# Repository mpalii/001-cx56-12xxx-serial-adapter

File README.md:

# 001-cx56-12xxx-serial-adapter
SN64HC595 based serial adapter for Cx54-21xxx displays

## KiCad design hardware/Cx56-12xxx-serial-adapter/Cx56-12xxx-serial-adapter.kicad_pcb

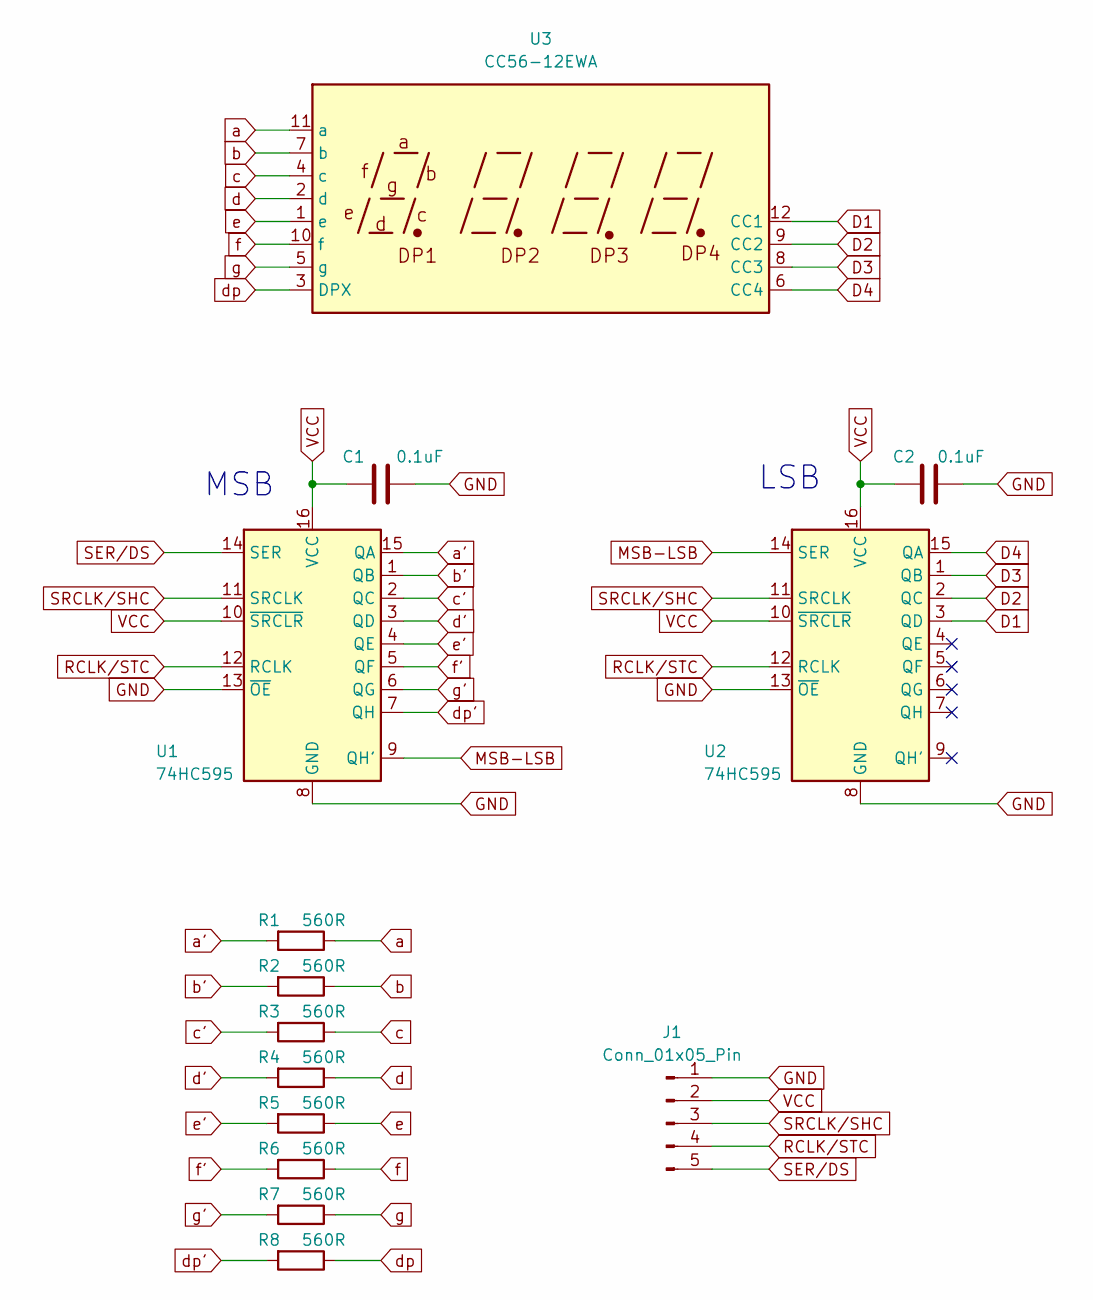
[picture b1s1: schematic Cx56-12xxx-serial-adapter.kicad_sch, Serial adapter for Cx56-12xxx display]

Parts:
C1, C2: 0.1uF; C_0805_2012Metric_Pad1.18x1.45mm_HandSolder
J1: Conn_01x05_Pin; PinHeader_1x05_P2.54mm_Horizontal
R1, R2, R3, R4, R5, R6, R7, R8: 560R; R_0805_2012Metric_Pad1.20x1.40mm_HandSolder
U1, U2: 74HC595; SOP-16_3.9x9.9mm_P1.27mm
U3: CC56-12EWA; CA56-12EWA

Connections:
D1: U2.3 (QD), U3.12 (CC1)
D2: U2.2 (QC), U3.9 (CC2)
D3: U2.1 (QB), U3.8 (CC3)
D4: U2.15 (QA), U3.6 (CC4)
GND: C1.2, C2.2, J1.1, U1.8 (GND), U1.13 (~OE), U2.8 (GND), U2.13 (~OE)
MSB-LSB: U1.9 (QH'), U2.14 (SER)
RCLK/STC: J1.4, U1.12 (RCLK), U2.12 (RCLK)
SER/DS: J1.5, U1.14 (SER)
SRCLK/SHC: J1.3, U1.11 (SRCLK), U2.11 (SRCLK)
VCC: C1.1, C2.1, J1.2, U1.10 (~SRCLR), U1.16 (VCC), U2.10 (~SRCLR), U2.16 (VCC)
a: R1.1, U3.11 (a)
a': R1.2, U1.15 (QA)
b: R2.1, U3.7 (b)
b': R2.2, U1.1 (QB)
c: R3.1, U3.4 (c)
c': R3.2, U1.2 (QC)
d: R4.1, U3.2 (d)
d': R4.2, U1.3 (QD)
dp: R8.1, U3.3 (DPX)
dp': R8.2, U1.7 (QH)
e: R5.1, U3.1 (e)
e': R5.2, U1.4 (QE)
f: R6.1, U3.10 (f)
f': R6.2, U1.5 (QF)
g: R7.1, U3.5 (g)
g': R7.2, U1.6 (QG)

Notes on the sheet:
MSB
LSB

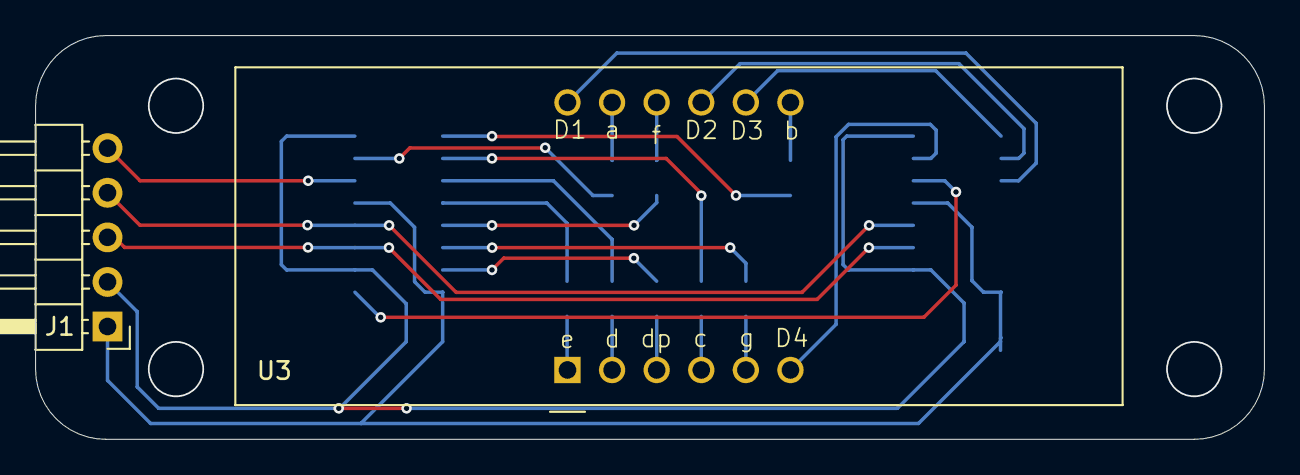
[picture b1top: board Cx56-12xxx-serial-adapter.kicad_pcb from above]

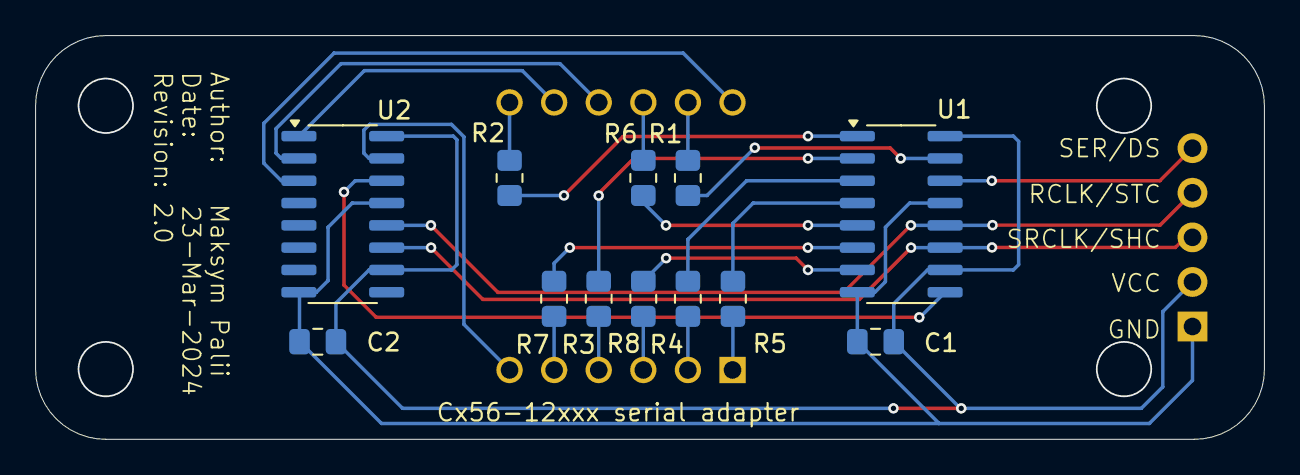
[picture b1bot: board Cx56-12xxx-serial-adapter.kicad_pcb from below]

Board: 2 copper layers, 70.0 x 23.0 mm, 14 parts (12 on the bottom side), 26 nets.

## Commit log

2024-03-23 001: basic implementation of serial adapter for Cx56-12xxx dynamic lighting
2024-03-23 002: from MSB to LSB shift register data transmission
